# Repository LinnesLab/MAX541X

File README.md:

# MAX541X  
**NOTE:**<br/>
This library appears to be broken. I should be able to fix it by sometime in February 2021.<br/>
Please use the MAX5419 library (https://github.com/LinnesLab/MAX5419) in the meantime. Thank<br/>
you to the user that brought the error to my attention.  
  
Arduino library for controlling the MAX5417, MAX5418, and MAX5419 Digital Potentiometers

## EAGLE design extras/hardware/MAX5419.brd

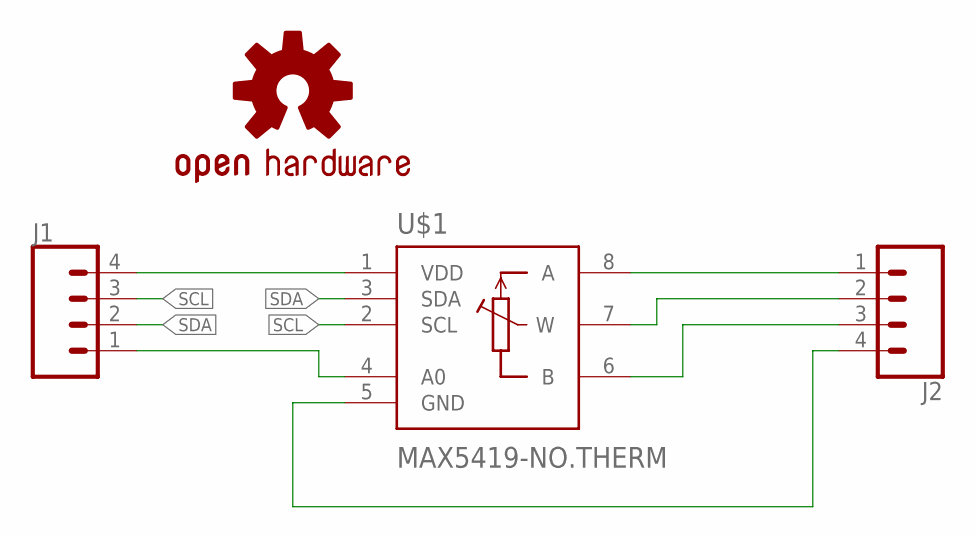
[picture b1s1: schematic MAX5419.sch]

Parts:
J1, J2: CONN_041X04_NO_SILK; 1X04_NO_SILK
LOGO1: OSHW-LOGOS; OSHW-LOGO-S
U$1: MAX5419-NO.THERM; TDFN8-3X3MM

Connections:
unnamed: J2.1, U$1.8 (A)
unnamed: J2.2, U$1.7 (W)
unnamed: J2.3, U$1.6 (B)
unnamed: J2.4, U$1.5 (GND)
unnamed: J1.4, U$1.1 (VDD)
unnamed: J1.1, U$1.4 (A0)
SCL: J1.3, U$1.2 (SCL)
SDA: J1.2, U$1.3 (SDA)

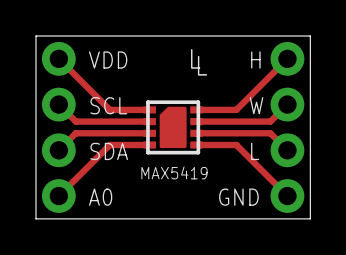
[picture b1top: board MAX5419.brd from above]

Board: 2 copper layers, 15.2 x 10.2 mm, 4 parts (1 on the bottom side), 8 nets.

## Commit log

2019-07-14 first official commit
2019-07-14 Add required paragraph field to library.properties
    When the paragraph field is missing from library.properties, the Arduino IDE does not recognize the library:
    - Sketch > Include Library > Add .ZIP Library fails silently.
    - Compilation of any code that includes the library fails.
    - After manual installation, "Invalid library" warnings are shown every time the libraries are scanned.
    - Library Manager index inclusion request is blocked.
    Reference:
